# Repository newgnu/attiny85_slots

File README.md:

# attiny85_slots
Slot machine toy using an attiny85, ssd1306, and a single button.

### Requirements
Uses SpenceKonde's ATTinyCore.  
in arduino settings, add http://drazzy.com/package_drazzy.com_index.json to the 'additional board manager urls', then the above will appear in your board manager as "ATTinyCore"  
Or pull it manually from https://github.com/SpenceKonde/ATTinyCore  
(Others will probably work too, but are untested)

The included ssd1306 tiny lib also uses SoftI2C (https://github.com/felias-fogg/SoftI2CMaster.git)  
It can be made to work with something like tinywire, but this lib is way faster.

Use 16MHZ PLL clock, Disable B.O.D, Timer 1 CPU, LTO Disabled. (Fuses: E:FF, H:D7, L:F1)

### Notes:
There are multiple different manufacturers making ssd1306 breakouts, and their pins are not always the same. This build uses the i2c version (not spi), with pins in the order vcc, gnd, scl, sda.  
Many swap the vcc/gnd pins, and that would end badly...

The board was designed as small and simple as possible. Realistically, it _should_ have a capacitor on the power pins of the attiny, some pull-up resistors on the i2c pins, and probably a pull-up resistor on the button.

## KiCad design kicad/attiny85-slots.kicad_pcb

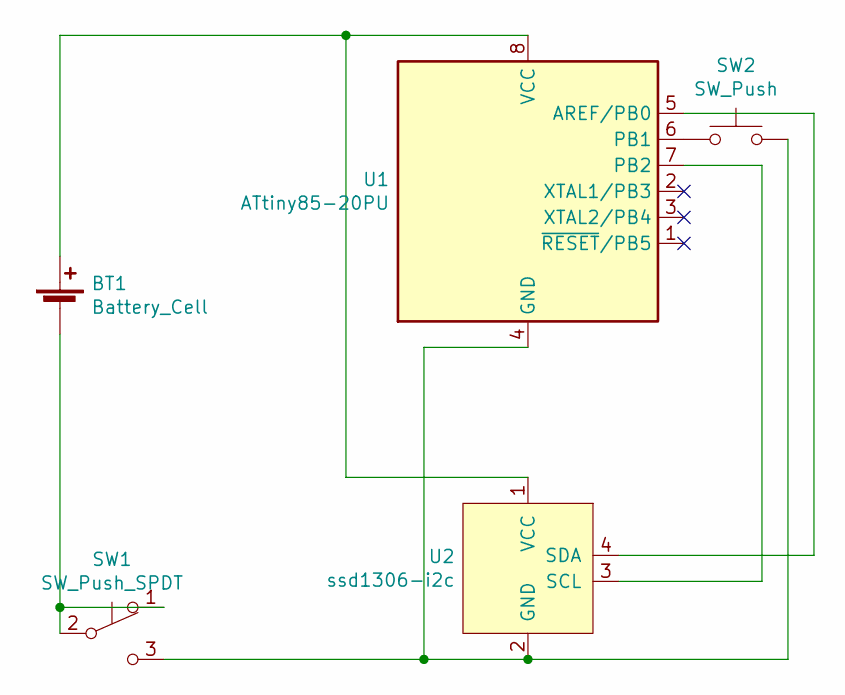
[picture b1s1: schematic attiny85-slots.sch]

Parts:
BT1: Battery_Cell; BatteryHolder_MPD_BC2003_1x2032
SW1: SW_Push_SPDT; PinHeader_1x03_P2.54mm_Vertical
SW2: SW_Push; SW_PUSH_6mm
U1: ATtiny85-20PU; DIP-8_W7.62mm
U2: ssd1306-i2c; PinHeader_1x04_P2.54mm_Vertical

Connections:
unnamed: BT1.1 (+), U1.8 (VCC), U2.1 (VCC)
unnamed: BT1.2 (-), SW1.1 (A), SW1.2 (B)
unnamed: SW1.3 (C), SW2.2, U1.4 (GND), U2.2 (GND)
unnamed: SW2.1, U1.6 (PB1)
unnamed: U1.5 (AREF/PB0), U2.4 (SDA)
unnamed: U1.7 (PB2), U2.3 (SCL)

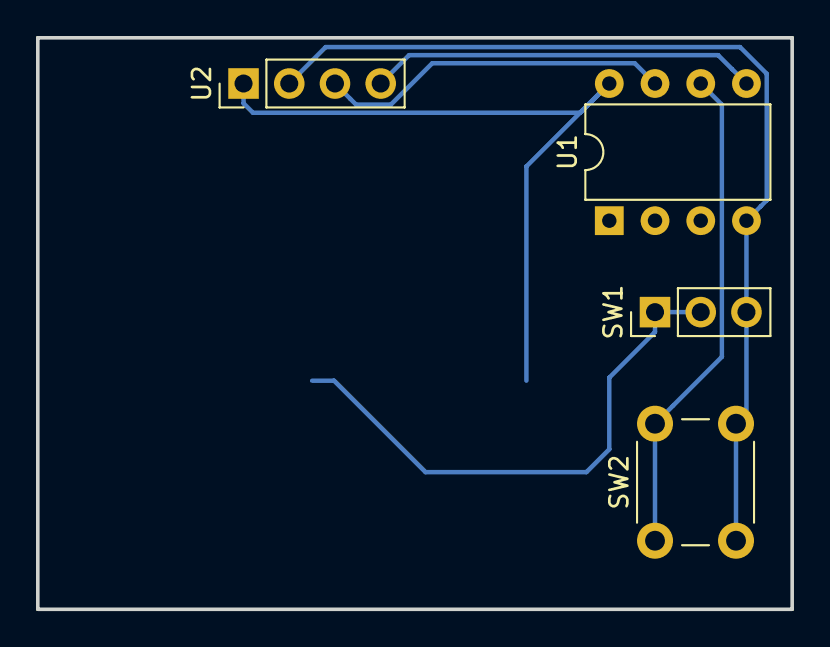
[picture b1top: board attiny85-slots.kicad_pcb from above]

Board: 2 copper layers, 41.9 x 31.8 mm, 5 parts (1 on the bottom side), 6 nets.

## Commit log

2019-02-13 Add board images
2019-02-13 Use gif demo in README
2021-05-05 enforce uisng int values when sending data via writeP
